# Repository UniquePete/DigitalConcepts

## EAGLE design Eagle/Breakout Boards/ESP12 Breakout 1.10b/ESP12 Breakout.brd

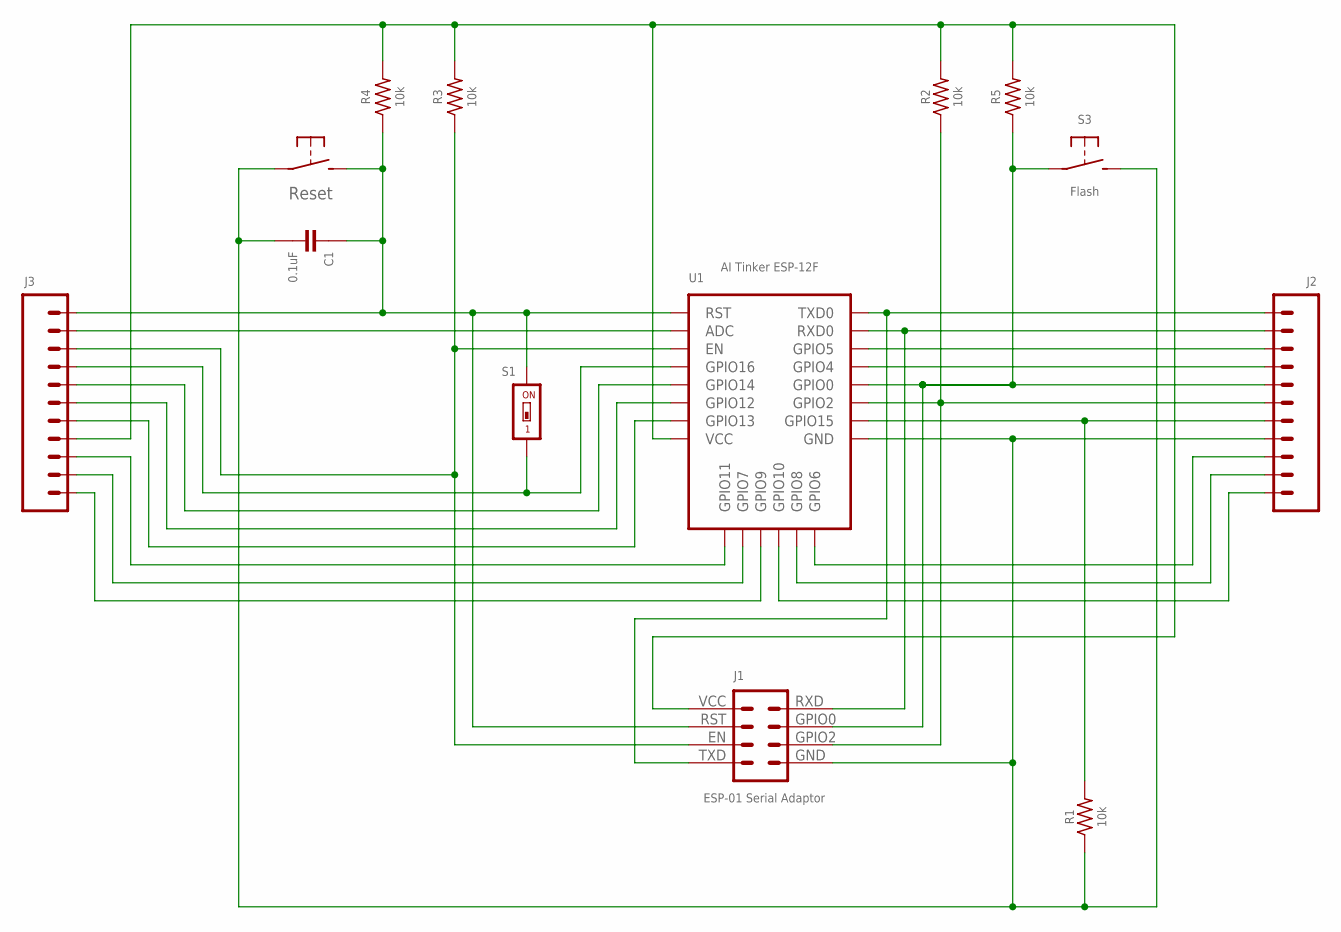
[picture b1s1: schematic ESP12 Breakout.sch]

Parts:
C1: 0.1uF; C0805
J1: ESP-01 Serial Adaptor; CONN_2X4-ESP-01-SERIAL
J2, J3: HEADER-1X11-GENERIC; CONN_11-GENERIC
R1, R2, R3, R4, R5: 10k; R0805
S1: Wake; SMD-001
S2: Reset; SWITCH-2-PAD
S3: Flash; SWITCH-2-PAD
U1: AI Tinker ESP-12F; ESP-12E/F

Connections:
GND: C1.2, J1.GND (1), J2.4, R1.1, S2.P$1, S3.P$2 (S), U1.GND
unnamed: J3.1, U1.GPIO9
unnamed: J2.5, R1.2, U1.GPIO15
unnamed: J3.7, U1.GPIO14
unnamed: C1.1, J1.RST (6), J3.11, R4.1, S1.2, S2.P$2 (S), U1.RST
unnamed: J3.6, U1.GPIO12
unnamed: J3.5, U1.GPIO13
unnamed: J3.10, U1.ADC
unnamed: J1.EN (7), J3.9, R3.1, U1.EN
unnamed: J2.9, U1.GPIO5
unnamed: J1.TXD (8), J2.11, U1.TXD0
unnamed: J1.GPIO2 (2), J2.6, R2.1, U1.GPIO2
unnamed: J2.8, U1.GPIO4
unnamed: J1.GPIO0 (3), J2.7, R5.1, S3.P$1, U1.GPIO0
unnamed: J2.1, U1.GPIO10
unnamed: J1.RXD (4), J2.10, U1.RXD0
unnamed: J2.3, U1.SCLK (GPIO6)
unnamed: J3.8, S1.1, U1.GPIO16
unnamed: J2.2, U1.MOSI (GPIO8)
unnamed: J3.3, U1.CS0 (GPIO11)
unnamed: J3.2, U1.MISO (GPIO7)
VCC: J1.VCC (5), J3.4, R2.2, R3.2, R4.2, R5.2, U1.VCC

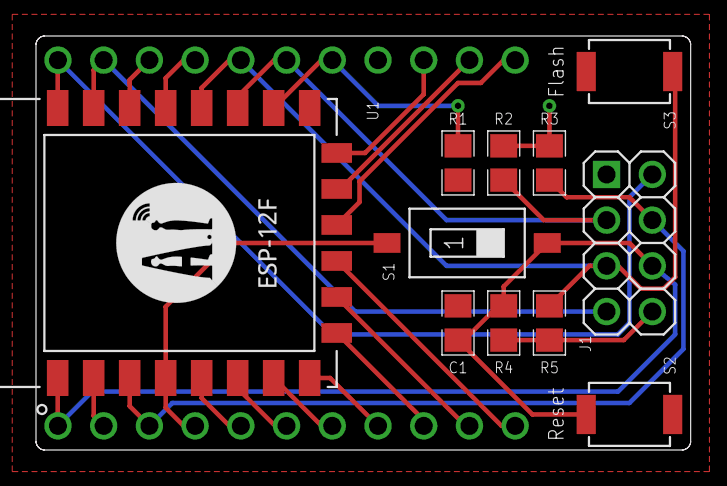
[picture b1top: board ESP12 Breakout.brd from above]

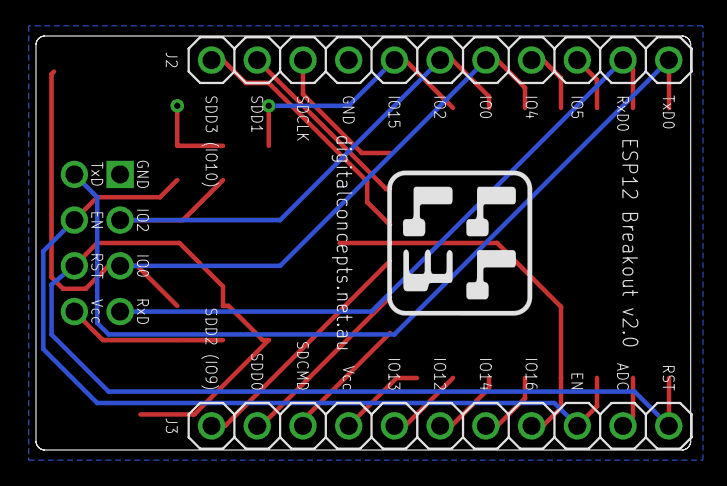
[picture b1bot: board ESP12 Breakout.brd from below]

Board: 2 copper layers, 36.4 x 23.0 mm, 13 parts (2 on the bottom side), 22 nets.

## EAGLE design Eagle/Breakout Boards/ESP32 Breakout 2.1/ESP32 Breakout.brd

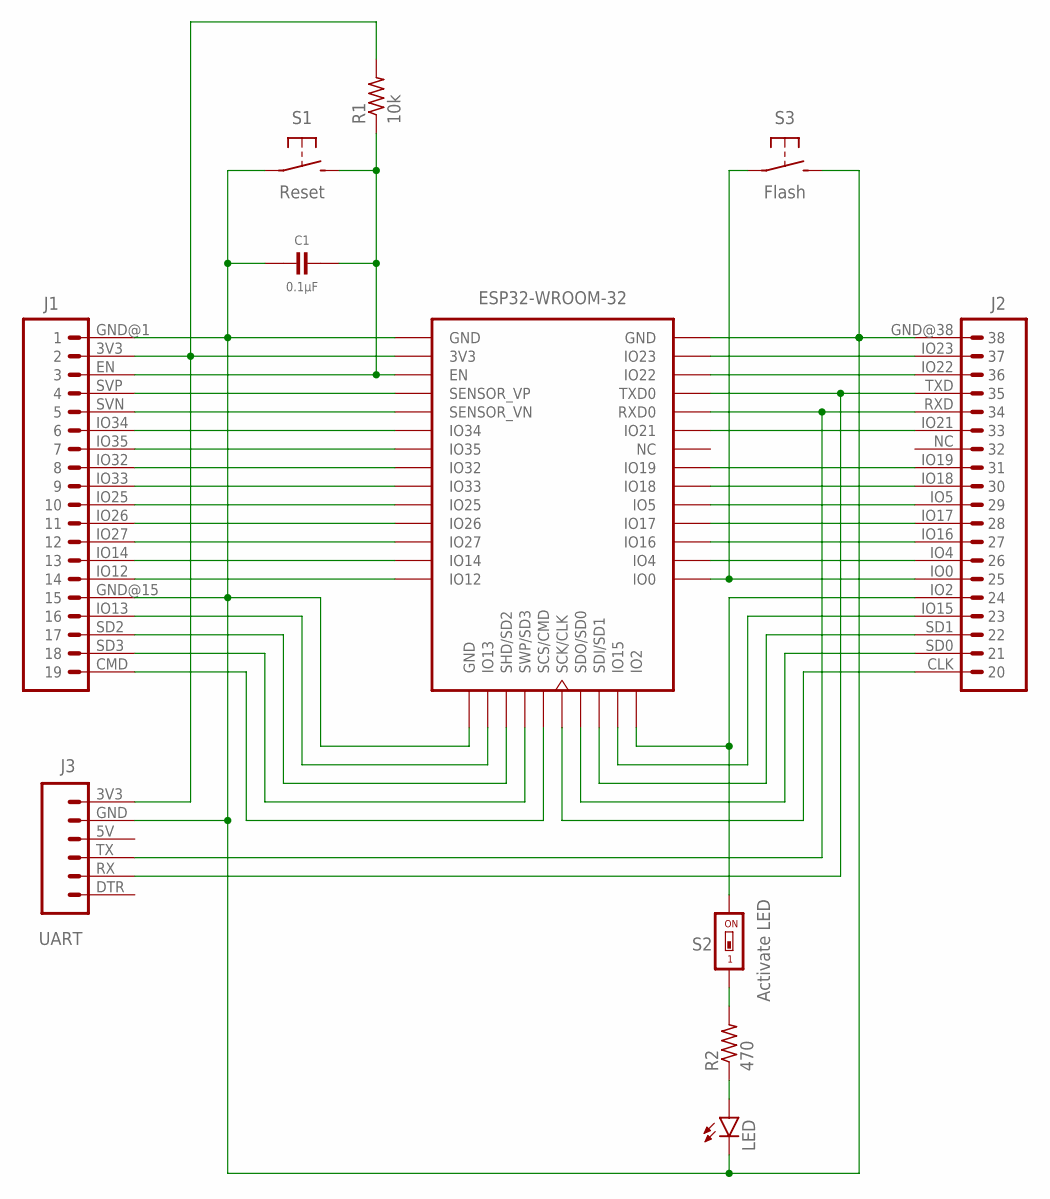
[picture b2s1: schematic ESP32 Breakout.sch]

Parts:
C1: 0.1µF; C0805
J1: HEADER-1X19-ESP32-L; CONN_19-ESP32-L
J2: HEADER-1X19-ESP32-R; CONN_19-ESP32-R
J3: UART; CONN_06-UART
LED: LEDCHIP-LED0805; CHIP-LED0805
R1: 10k; R0805-VIA-2
R2: 470; R0805
S1: Reset; SWITCH-2-PAD
S2: Activate LED; SMD-001
S3: Flash; SWITCH-2-PAD
U1: ESP32-WROOM-32

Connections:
GND: C1.2, J1.GND@1 (1), J1.GND@15 (15), J2.GND@38 (38), J3.GND (5), LED.C, S1.P$1, S3.P$2 (S), U1.GND@1 (GND), U1.GND@15 (GND), U1.GND@38 (GND), U1.TP (GND), U1.TP@P1 (GND), U1.TP@P2 (GND), U1.TP@P3 (GND), U1.TP@P4 (GND), U1.TP@P5 (GND), U1.TP@P6 (GND), U1.TP@P7 (GND), U1.TP@P8 (GND), U1.TP@P9 (GND), U1.TP@V1 (GND), U1.TP@V2 (GND), U1.TP@V3 (GND), U1.TP@V4 (GND), U1.TP@V5 (GND), U1.TP@V6 (GND), U1.TP@V7 (GND), U1.TP@V8 (GND), U1.TP@V9 (GND), U1.TP@V10 (GND), U1.TP@V11 (GND), U1.TP@V12 (GND), U1.TP@VP5 (GND)
unnamed: R2.2, S2.1
unnamed: J1.SVP (4), U1.SENSOR_VP
unnamed: C1.1, J1.EN (3), R1.1, S1.P$2 (S), U1.EN
unnamed: J1.IO32 (8), U1.IO32
unnamed: J1.SVN (5), U1.SENSOR_VN
unnamed: J1.IO34 (6), U1.IO34
unnamed: J1.IO35 (7), U1.IO35
unnamed: LED.A, R2.1
unnamed: J2.IO19 (31), U1.IO19
unnamed: J2.IO17 (28), U1.IO17
unnamed: J1.CMD (19), U1.CMD (SCS/CMD)
unnamed: J2.IO18 (30), U1.IO18
unnamed: J2.IO22 (36), U1.IO22
unnamed: J2.IO15 (23), U1.IO15
unnamed: J2.CLK (20), U1.CLK (SCK/CLK)
unnamed: J2.SD0 (21), U1.SD0 (SDO/SD0)
unnamed: J2.SD1 (22), U1.SD1 (SDI/SD1)
unnamed: J2.IO23 (37), U1.IO23
unnamed: J2.IO2 (24), S2.2, U1.IO2
unnamed: J2.IO0 (25), S3.P$1, U1.IO0
unnamed: J2.IO4 (26), U1.IO4
unnamed: J2.IO16 (27), U1.IO16
unnamed: J2.IO5 (29), U1.IO5
unnamed: J2.RXD (34), J3.TX (3), U1.RXD0
unnamed: J2.TXD (35), J3.RX (2), U1.TXD0
unnamed: J2.IO21 (33), U1.IO21
unnamed: J1.IO33 (9), U1.IO33
unnamed: J1.IO25 (10), U1.IO25
unnamed: J1.IO26 (11), U1.IO26
unnamed: J1.IO27 (12), U1.IO27
unnamed: J1.IO14 (13), U1.IO14
unnamed: J1.IO12 (14), U1.IO12
unnamed: J1.SD2 (17), U1.SD2 (SHD/SD2)
unnamed: J1.IO13 (16), U1.IO13
unnamed: J1.SD3 (18), U1.SD3 (SWP/SD3)
VCC: J1.3V3 (2), J3.3V3 (6), R1.2, R1.2@VIA (2), U1.3V3

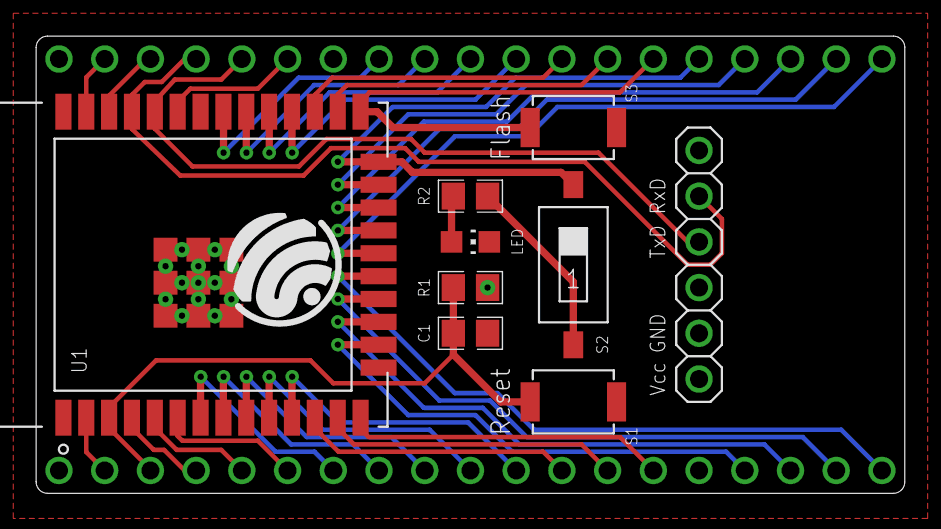
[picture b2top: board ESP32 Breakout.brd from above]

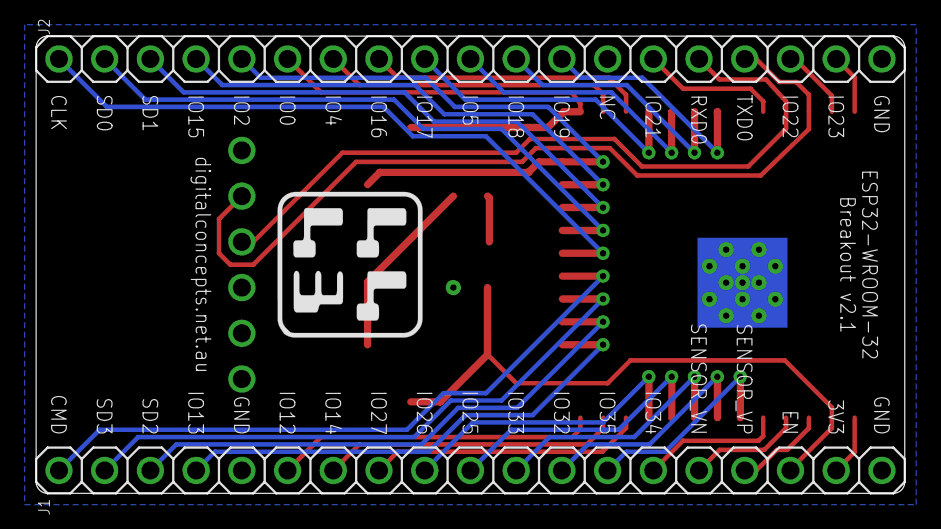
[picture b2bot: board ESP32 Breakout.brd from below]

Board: 2 copper layers, 48.3 x 25.4 mm, 11 parts (2 on the bottom side), 37 nets.

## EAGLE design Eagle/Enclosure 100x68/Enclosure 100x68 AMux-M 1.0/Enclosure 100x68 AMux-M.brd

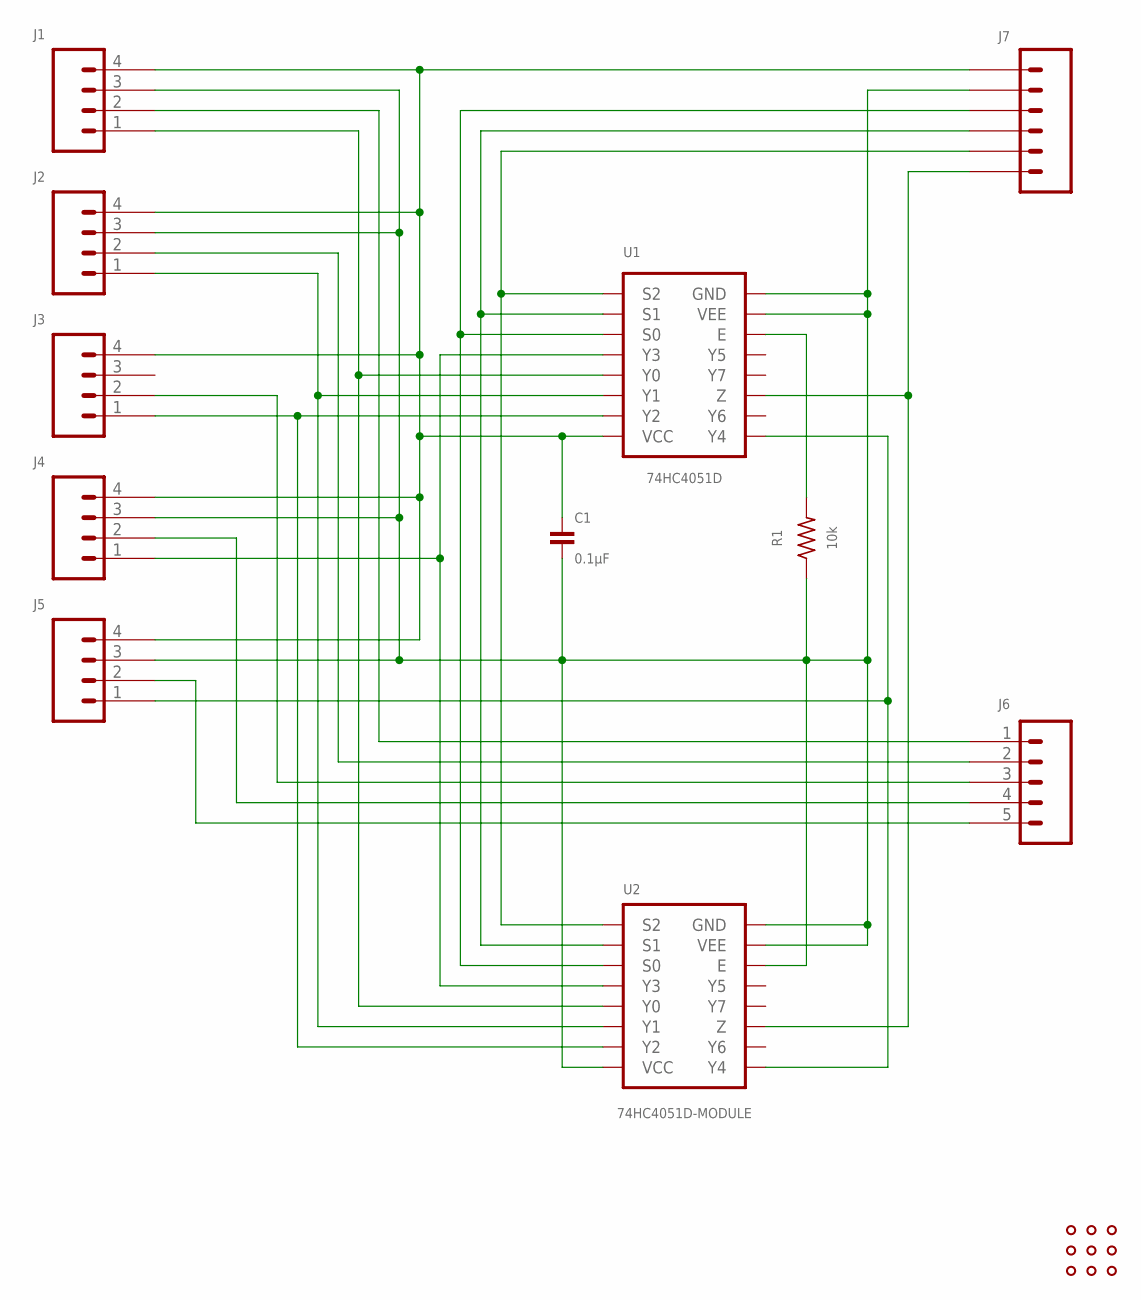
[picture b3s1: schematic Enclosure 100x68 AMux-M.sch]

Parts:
C1: 0.1µF; C0805
J1, J2, J3, J4, J5: HEADER-1X4-GENERIC; CONN_04-GENERIC
J6: JST-PH2.0-5-HORIZONTAL
J7: JST-PH2.0-6-HORIZONTAL
R1: 10k; R0805
U1: 74HC4051D; SOP16
U2: 74HC4051D-MODULE
U$1: PROTO-34X22-AMUX

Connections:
GND: C1.2, J1.3, J2.3, J4.3, J5.3, J7.2, R1.1, U1.7 (VEE), U1.8 (GND), U2.E, U2.GND@L (GND), U2.GND@R (GND), U2.VCC@L (VCC), U2.VCC@R (VCC), U2.VEE@L (VEE), U2.VEE@R (VEE)
unnamed: J4.1, U1.12 (Y3), U2.Y3
unnamed: J2.1, U1.14 (Y1), U2.Y1
unnamed: J1.1, U1.13 (Y0), U2.Y0
unnamed: J3.1, U1.15 (Y2), U2.Y2
unnamed: J5.1, U1.1 (Y4), U2.Y4
unnamed: J7.3, U1.11 (S0), U2.S0
unnamed: J7.4, U1.10 (S1), U2.S1
unnamed: R1.2, U1.6 (E)
unnamed: J7.6, U1.3 (Z), U2.Z
unnamed: J1.2, J6.1
unnamed: J7.5, U1.9 (S2), U2.S2
unnamed: J2.2, J6.2
unnamed: J3.2, J6.3
unnamed: J4.2, J6.4
unnamed: J5.2, J6.5
unnamed: C1.1, J1.4, J2.4, J3.4, J4.4, J5.4, J7.1, U1.16 (VCC)

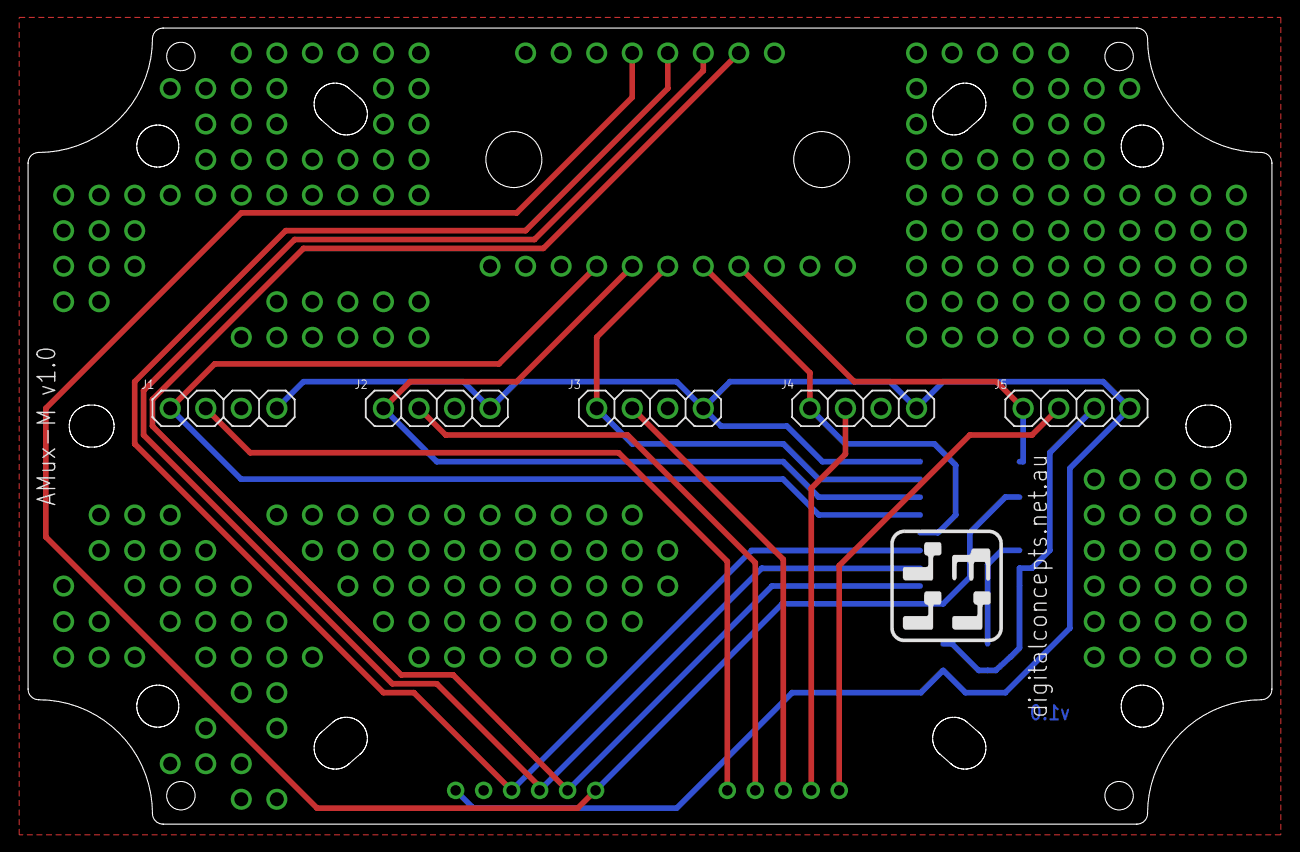
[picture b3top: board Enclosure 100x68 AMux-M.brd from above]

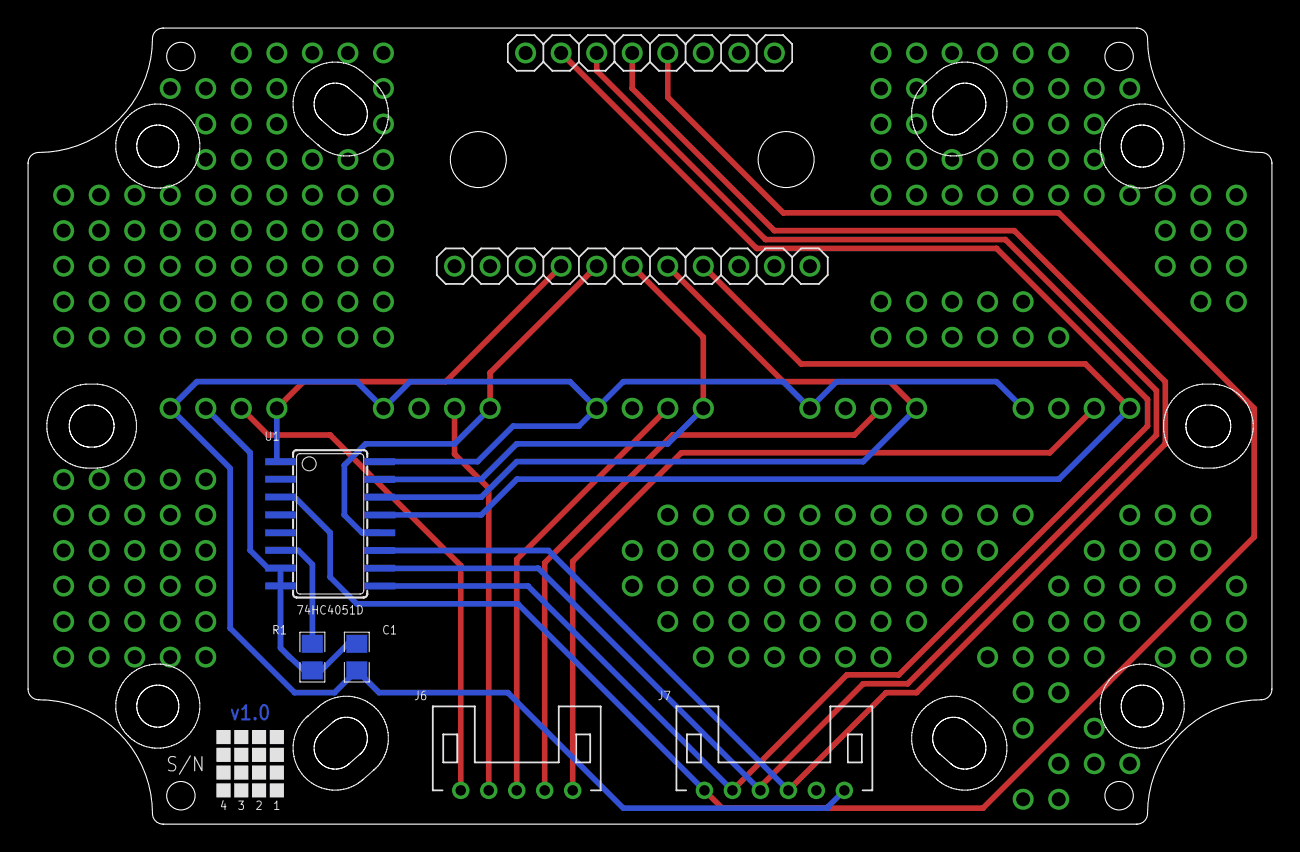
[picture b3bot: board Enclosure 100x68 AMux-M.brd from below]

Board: 2 copper layers, 88.9 x 56.9 mm, 12 parts (6 on the bottom side), 17 nets.

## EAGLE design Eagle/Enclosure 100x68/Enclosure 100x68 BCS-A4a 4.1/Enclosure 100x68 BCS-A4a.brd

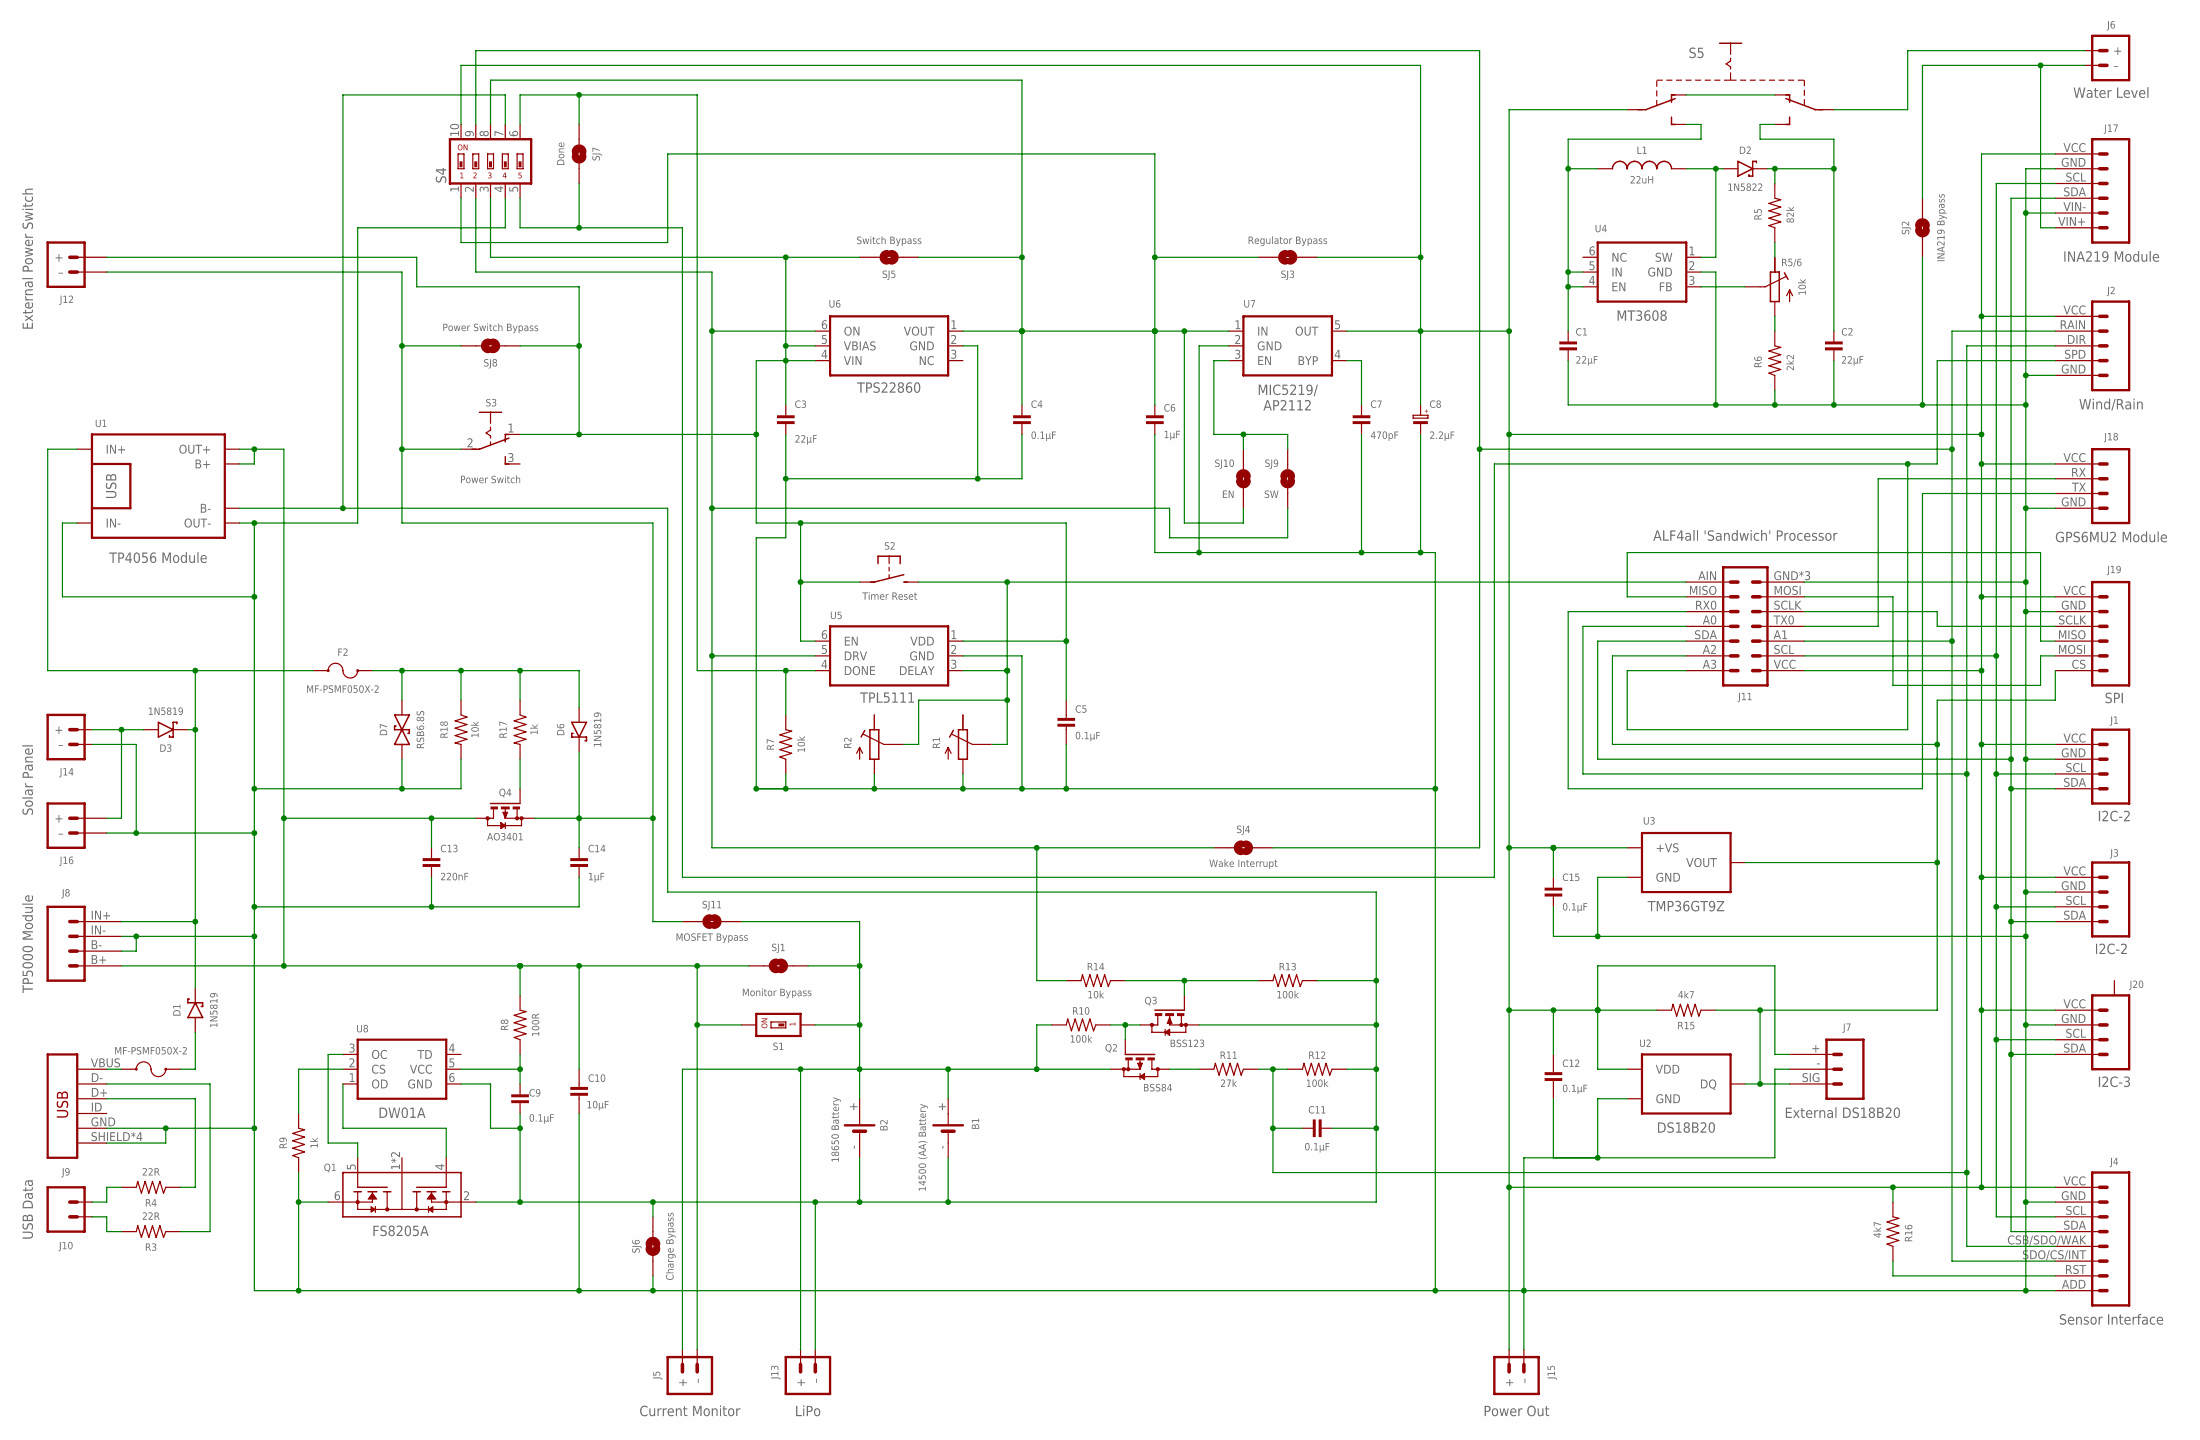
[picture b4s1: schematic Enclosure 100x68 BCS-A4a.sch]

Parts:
B1: 14500 (AA) Battery; BATTERY-14500
B2: 18650 Battery; BATTERY-18650
C1, C2: 22µF; C1206
C3: 22µF; C0805
C4, C9, C11, C15: 0.1µF; C0805
C5: 0.1µF; C0805@1
C6, C14: 1µF; C0805
C7: 470pF; C0805
C8: 2.2µF; C1206-POLARISED
C10: 10µF; C0805-VIA-2@1
C12: 0.1µF; C0805-VIA-2@1
C13: 220nF; C0805
D1, D3, D6: 1N5819; SOD-123
D2: 1N5822; DIODE_SMB
D7: RSB6.8S; VMD2
F1, F2: MF-PSMF050X-2; F0805
J1: I2C-2; JST-PH2.0-4-DUAL-I2C
J2: Wind/Rain; JST-PH2.0-5-DUAL-WEATHER
J3: I2C-2; CONN_04-I2C
J4: Sensor Interface; CONN_08-SENSOR
J5: Current Monitor; JST-PH2.0-2-HORIZONTAL
J6: Water Level; JST-PH2.0-2-VERTICAL
J7: External DS18B20; JST-PH2.0-DS18B20-HORIZONTAL
J8: TP5000 Module; CONN_04-TP5000
J9: USB; USB-MINIB
J10: USB Data; CONN_02-GENERIC
J11: ALF4all 'Sandwich' Processor; ALF4ALL-PROCESSOR-BOARD
J12: External Power Switch; JST-PH2.0-2-DUAL-POWER
J13: LiPo; JST-PH2.0-2-HORIZONTAL
J14: Solar Panel; JST-PH2.0-2-VERTICAL=POWER
J15: Power Out; JST-SH1.25-2-VERTICAL
J16: JST-PH2.0-2-HORIZONTAL-POWERJST-PTH-2; JST-PH2.0-2-HORIZONTAL-POWER
J17: INA219 Module; CONN_06-INA219
J18: GPS6MU2 Module; CONN_04-GPS
J19: SPI; JST-PH2.0-6-HORIZONTAL-SPI
J20: I2C-3; JST-SH1.0-4-I2C-HORIZONTAL
L1: 22uH; CDRH104R+6D28
Q1: FS8205A; FS8205-SOP?
Q2: BSS84; SOT23-3@1
Q3: BSS123; SOT23-3
Q4: AO3401; SOT-23
R1: RESISTOR-TRIMM-BAOTER-VERTICAL; RTRIM3296
R2: RESISTOR-TRIMM-33; RTRIM3*3
R3, R4: 22R; R0805-VIA-1
R5: 82k; R0805
R5/6: 10k; RTRIM64P
R6: 2k2; R0805
R7, R14, R18: 10k; R0805
R8: 100R; R0805
R9, R17: 1k; R0805
R10, R12, R13: 100k; R0805
R11: 27k; R0805
R15, R16: 4k7; R0805
S1: Monitor Bypass; SMD-001-VIA-1
S2: Timer Reset; SWITCH-2-PAD-VIA-1
S3: Power Switch; SWITCH-SPDT-PTH
S4: SWITCH-DIP-SWS005; SMD-005
S5: SWITCH-SLIDE-DPDT-PTH-S; SWITCH-DPDT-PTH
SJ1: Monitor Bypass; SJ
SJ2: INA219 Bypass; SJ
SJ3: Regulator Bypass; SJ-VIA-12
SJ4: Wake Interrupt; SJ-VIA-1
SJ5: Switch Bypass; SJ-VIA-1
SJ6: Charge Bypass; SJ-VIA-1
SJ7: Done; SJ-VIA-1
SJ8: Power Switch Bypass; SJ
SJ9: SW; SJ
SJ10: EN; SJ
SJ11: MOSFET Bypass; SJ
U1: TP4056 Module; BATTERY-CHARGER-LI-PROT
U2: DS18B20; TO-92
U3: TMP36GT9Z; TO-92
U4: MT3608; SOT-23-6
U5: TPL5111; SOT-23-6
U6: TPS22860; SOT-23-6
U7: MIC5219; SOT-23-5
U8: DW01A; SOT-23-6

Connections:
GND: C1.2, C2.2, C3.2, C4.1, C5.1, C6.2, C7.2, C8.2 (-), C10.2, C10.2@VIA (2), C12.2, C12.2@VIA (2), C13.2, C14.2, C15.2, D7.P$2 (2), J1.GND (2), J2.GND (1), J3.GND (2), J4.ADD (8), J4.GND (2), J7.- (2), J8.B- (2), J8.IN- (3), J9.GND, J9.SHIELD, J9.SHIELD@2 (SHIELD), J9.SHIELD@3 (SHIELD), J9.SHIELD@4 (SHIELD), J11.GND (7), J11.GND@TL (7), J11.GND@TR (7), J14.- (–), J15.- (–), J16.- (–), J17.GND (2), J17.VIN- (5), J18.GND (1), J19.GND (5), J20.GND (3), Q1.6 (S2), R1.1 (A), R2.1 (A), R6.1, R7.1, R9.1, R18.2, S4.4, SJ2.1, SJ6.1, SJ6.1@V (1), U1.IN-, U1.OUT-, U2.1 (GND), U3.3 (GND), U4.2 (GND), U5.2 (GND), U6.2 (GND), U7.2 (GND)
unnamed: D3.A, J14.+, J16.+
unnamed: C4.2, C6.1, S4.1, S4.8, SJ3.2, SJ3.2@V (2), SJ5.1, SJ5.1@V (1), SJ10.2, U6.1 (VOUT), U7.1 (IN)
unnamed: R9.2, U8.2 (CS)
unnamed: J10.2, R4.2
unnamed: R7.2, S4.6, SJ7.1, SJ7.1@V (1), U5.4 (DONE)
unnamed: D2.A, L1.1, U4.1 (SW)
unnamed: C7.1, U7.4 (BYP)
unnamed: J1.SCL (3), J3.SCL (3), J4.SCL (3), J11.SCL (2), J17.SCL (3), J20.SCL (2)
unnamed: J4.RST (7), R16.1
unnamed: C11.1, J2.DIR (3), J4.CSB/SDO/WAK (5), J11.A0 (11), R11.1, R12.2
unnamed: J1.SDA (4), J3.SDA (4), J4.SDA (4), J11.SDA (12), J17.SDA (4), J20.SDA (1)
unnamed: B1.+, B2.+, J5.+, J13.+, Q2.2 (S), R10.2, S1.1, S1.1@VIA (1), SJ1.1, SJ11.2
unnamed: R5.1, R5/6.3 (E)
unnamed: J11.TX0 (4), J18.RX (3)
unnamed: J6.- (–), J17.VIN+ (6), SJ2.2
unnamed: J11.RX0 (10), J18.TX (2)
unnamed: Q1.5 (G2), U8.3 (OC)
unnamed: F1.2, J9.VBUS
unnamed: Q1.4 (G1), U8.1 (OD)
unnamed: J9.D+, R4.1, R4.1@VIA (1)
unnamed: C9.1, R8.1, U8.5 (VCC)
unnamed: Q2.3 (D), R11.2
unnamed: J9.D-, R3.1, R3.1@VIA (1)
unnamed: J11.AIN (8), R1.2 (S), R2.2 (S), S2.2 (S), U5.3 (DELAY)
unnamed: C3.1, C5.2, J12.+, S2.1, S2.1@VIA, S3.1 (O), S4.3, SJ5.2, SJ8.1, U5.1 (VDD), U5.6 (EN), U6.4 (VIN), U6.5 (VBIAS)
unnamed: R5/6.1 (A), R6.2
unnamed: R14.2, S4.2, SJ4.2, SJ9.2, U5.5 (DRV), U6.6 (ON)
unnamed: J2.SPD (2), J11.A3 (14), S4.5, SJ7.2
unnamed: J2.RAIN (4), J4.SDO/CS/INT (6), J11.A1 (3), S4.9, SJ4.1, SJ4.1@V (1)
unnamed: R5/6.2 (S), U4.3 (FB)
unnamed: C2.1, D2.C, R5.2, S5.P$6 (S2)
unnamed: S5.P$1 (O1), S5.P$4 (O2)
unnamed: C10.1, C13.1, J5.- (–), J8.B+ (1), Q4.3 (D), R8.2, S1.2, SJ1.2, U1.B+, U1.OUT+
unnamed: Q2.1 (G), Q3.3 (D), R10.1
unnamed: J6.+, S5.P$5 (P2)
unnamed: Q3.1 (G), R13.2, R14.1
unnamed: B1.-, B2.-, C9.2, C11.2, J13.- (–), Q1.2 (S1), Q3.2 (S), R12.1, R13.1, S4.7, SJ6.2, U1.B-, U8.6 (GND)
unnamed: C1.1, L1.2, S5.P$3 (S1), U4.4 (EN), U4.5 (IN)
unnamed: C14.1, D6.C, J12.- (–), Q4.2 (S), S3.2, SJ8.2, SJ11.1
unnamed: D1.C, D3.C, F2.1, J8.IN+ (4), U1.IN+
unnamed: J10.1, R3.2
unnamed: Q4.1 (G), R17.2
unnamed: D6.A, D7.P$1 (1), F2.2, R17.1, R18.1
unnamed: D1.A, F1.1
unnamed: SJ9.1, SJ10.1, U7.3 (EN)
unnamed: J11.SCLK (5), J19.SCLK (4)
unnamed: J11.MOSI (6), J19.MOSI (2)
unnamed: J7.SIG (1), J11.A2 (13), J19.CS (1), R15.1, U2.2 (DQ), U3.2 (VOUT)
unnamed: J11.MISO (9), J19.MISO (3)
VCC: C8.1 (+), C12.1, C15.1, J1.VCC (1), J2.VCC (5), J3.VCC (1), J4.VCC (1), J7.+ (3), J11.VCC (1), J15.+, J17.VCC (1), J18.VCC (4), J19.VCC (6), J20.VCC (4), R15.2, R16.2, S4.10, S5.P$2 (P1), SJ3.1, SJ3.1@V (1), U2.3 (VDD), U3.1 (+VS), U7.5 (OUT)

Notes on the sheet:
MIC5219/ AP2112

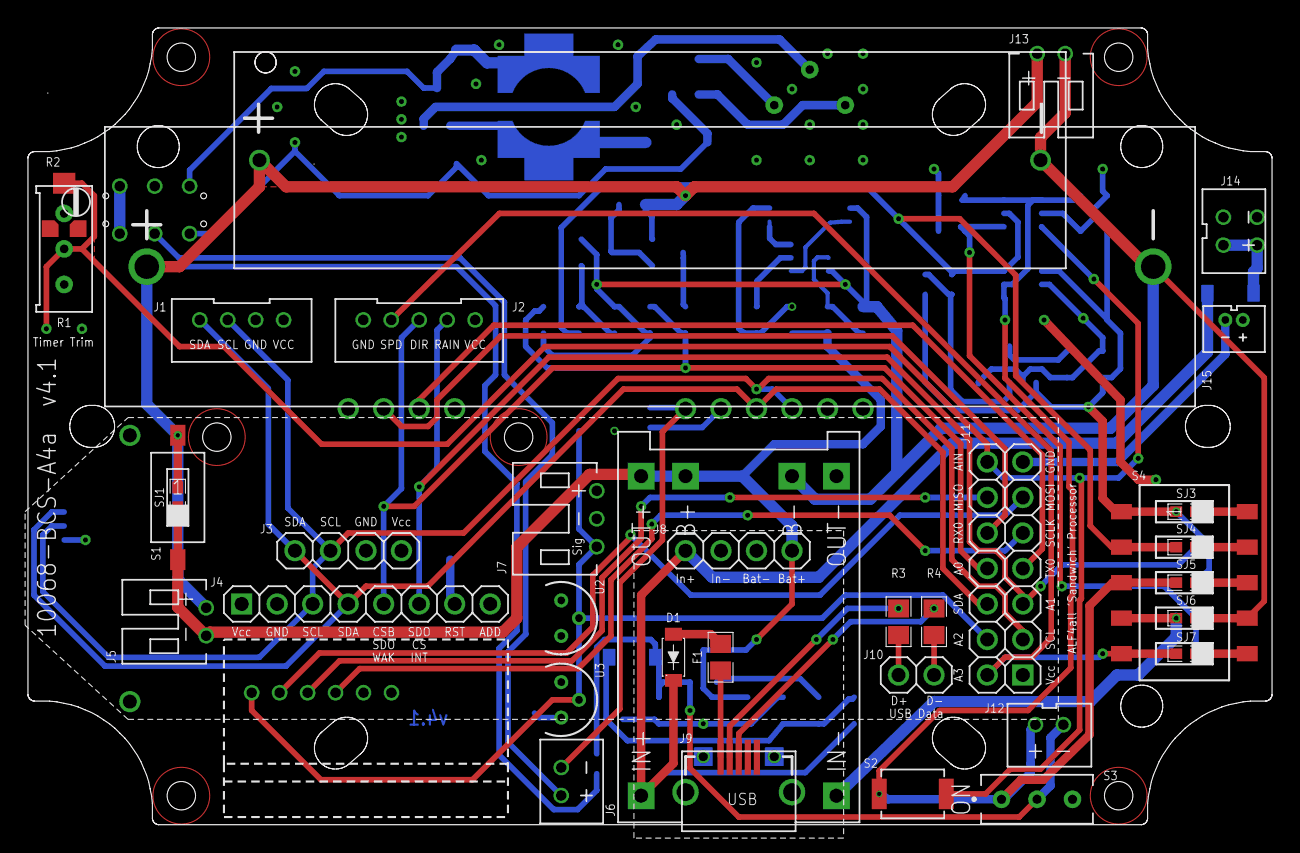
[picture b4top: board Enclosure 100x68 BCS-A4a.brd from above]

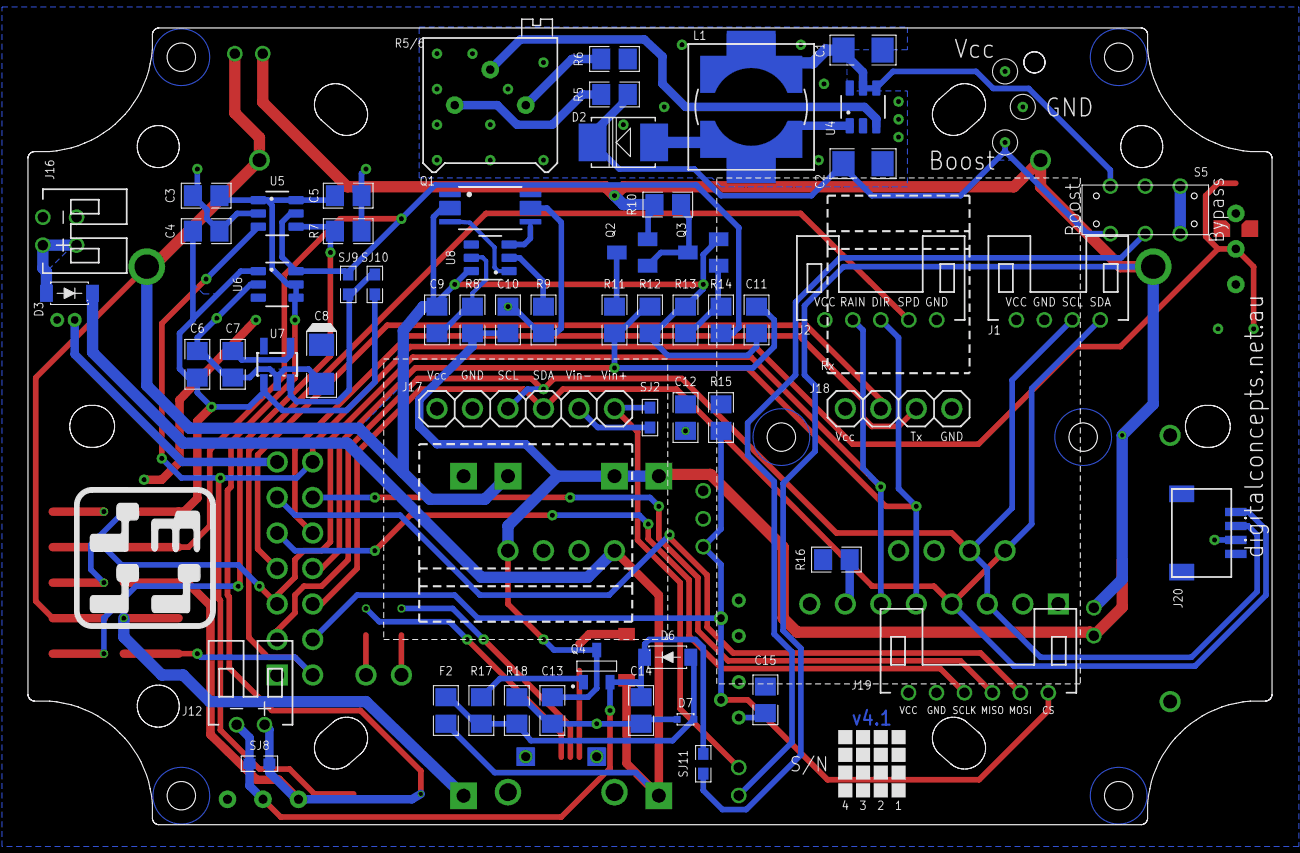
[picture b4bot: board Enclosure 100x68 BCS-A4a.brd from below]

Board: 2 copper layers, 89.0 x 57.0 mm, 92 parts (59 on the bottom side), 51 nets.
